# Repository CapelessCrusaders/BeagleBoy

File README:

This project is an entry in the Texas Instruments Intern Design Challenge 2013.
It is a cape for the BeagleBone Black which turns the BBB into a handheld 
gaming console with the addition of an LCD cape stacked on top or a controller
when connected to an HDMI monitor.

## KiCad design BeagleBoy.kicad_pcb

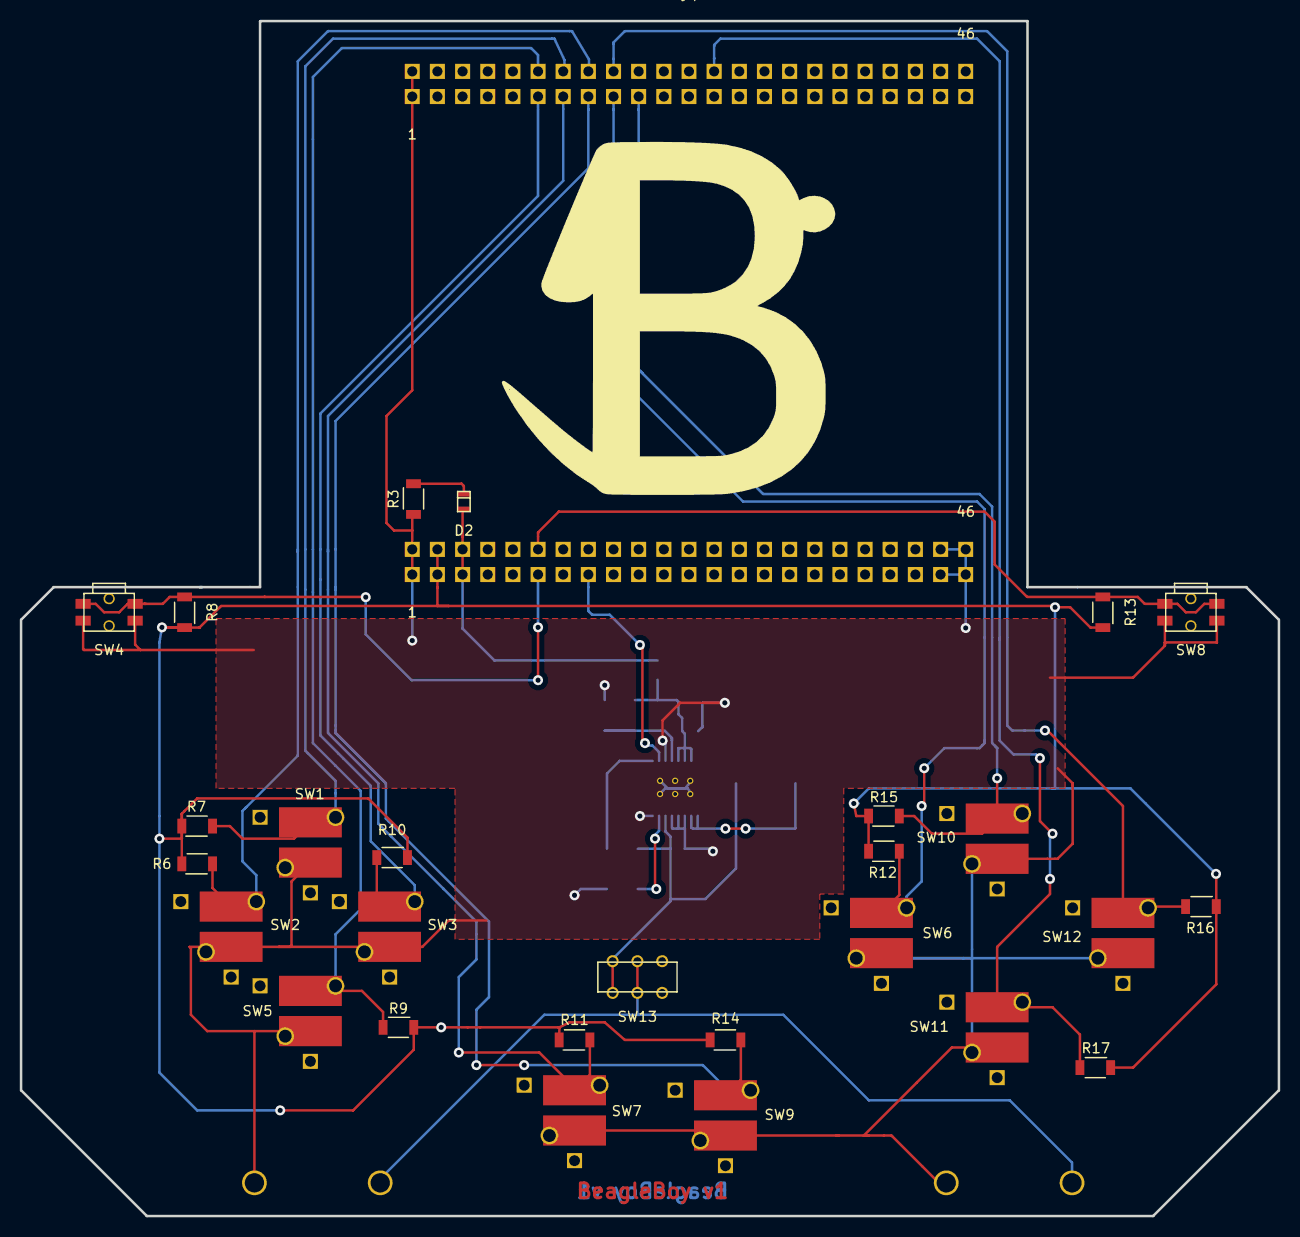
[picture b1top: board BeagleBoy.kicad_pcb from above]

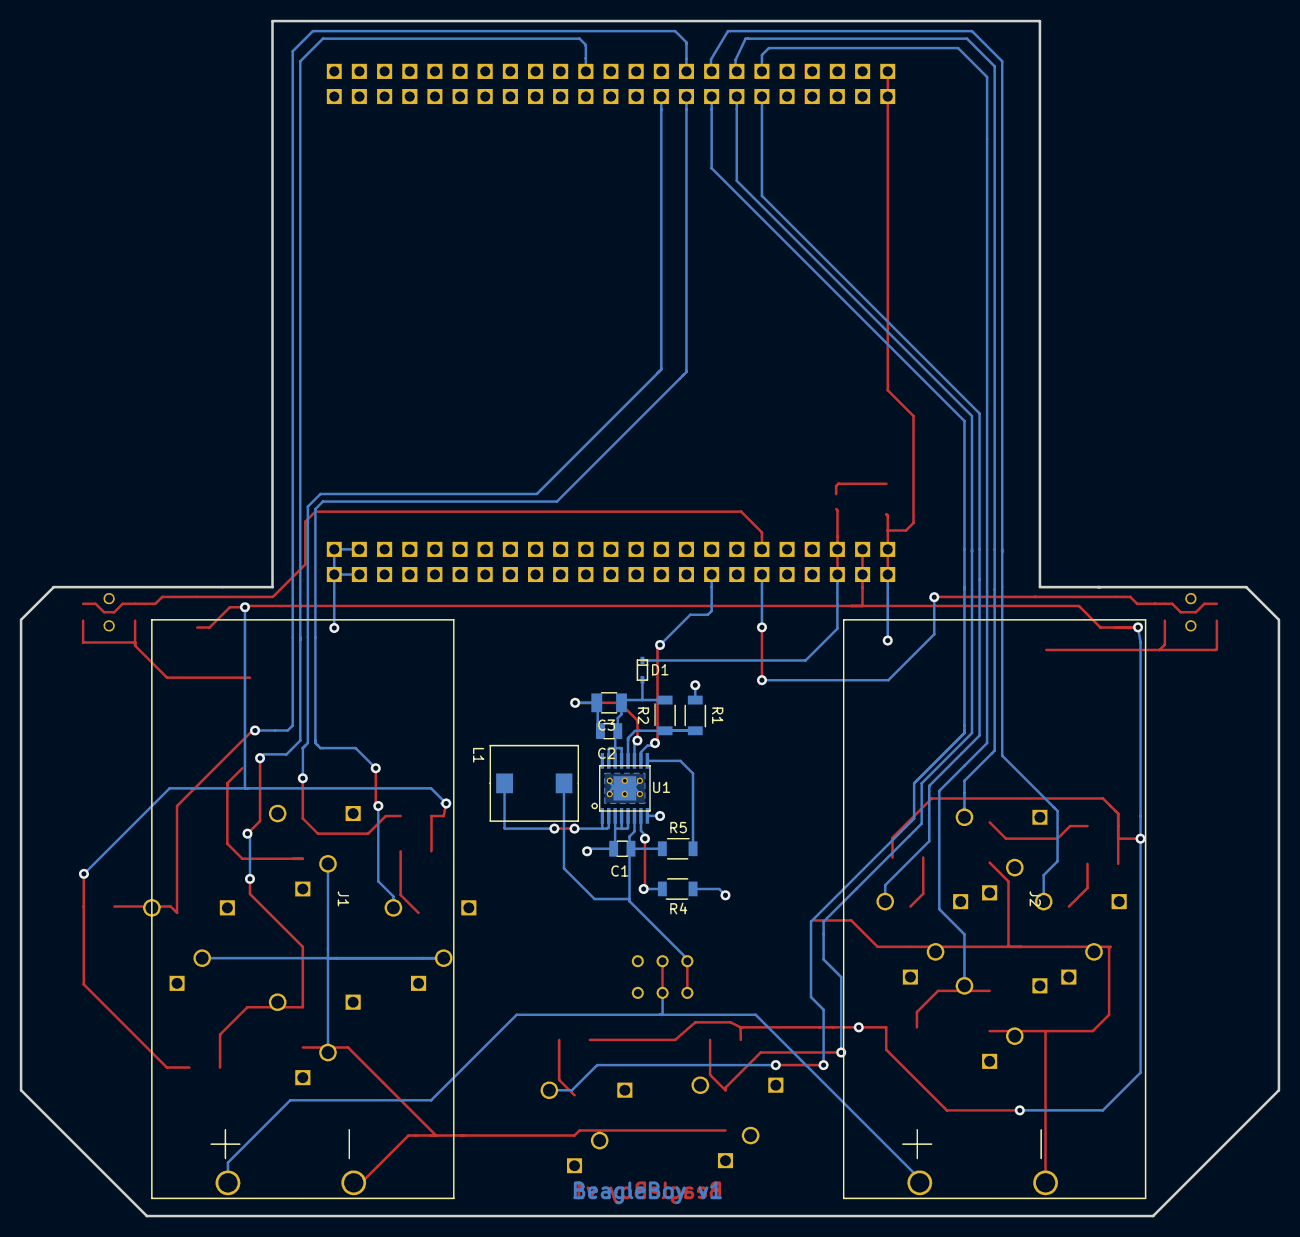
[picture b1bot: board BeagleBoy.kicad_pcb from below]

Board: 2 copper layers, 127.0 x 120.6 mm, 47 parts (12 on the bottom side), 24 nets.

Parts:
C1, C2: 10uF; 0805cap
C3: 47uF; 1206CAP
D1: DIODE_SHOTTKEY; PMEG1020EJ
D2: LED; LTST-C171KGKT
J1, J2: 2AA_BATT; BH2AAPC
J3, J4: 23X2; SSHQ-123-D-**-F-LF
J5, J6, J7, J8, J9, J10: 33MM_PAD; 33mm_pad
L1: 6.8uH; WE-PD
R1: 180K; 1206_resistor
R2: 1.74M; 1206_resistor
R3: 510; 1206_resistor
R4: 0; 1206_resistor
R5, R6, R7, R8, R9, R10, R11, R12, R13, R14, R15, R16, R17: 10K; 1206_resistor
SW1, SW2, SW3, SW5, SW6, SW7, SW9, SW10, SW11, SW12: SPST; SNES_switch
SW4, SW8: SPST_EVQ; EVQ-PUL02K
SW13: SPDT; MHSS1104
U1: TPS61032PWP

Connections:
+3.3V: J3.3, J3.4, R6.2, R7.2, R8.2, R9.2, R10.2, R11.2, R12.2, R13.2, R14.2, R15.2, R16.2, R17.2
+5V: D1.1, D2.1, J3.5, J3.6
+BATT: J1.2, J2.2, SW13.2, SW13.5
/EHRPWM2A: J4.19, R15.1, SW10.1, SW10.3
/EHRPWM2B: J4.13, R11.1, SW7.1, SW7.3
/EN: R5.2, U1.9
/FB: R1.2, R2.1, U1.12
/GPIO0_26: J4.14, R7.1, SW1.1, SW1.3
/GPIO0_27: J4.17, R12.1, SW6.1, SW6.3
/GPIO1_12: J4.12, R9.1, SW5.1, SW5.3
/GPIO1_13: J4.11, R10.1, SW3.1, SW3.3
/GPIO1_14: J4.16, R6.1, SW2.1, SW2.3
/GPIO1_15: J4.15, R14.1, SW9.1, SW9.3
/GPIO1_16: J3.15, U1.10
/GPIO1_28: J3.12, R13.1, SW8.2, SW8.4
/GPIO1_29: J4.26, R17.1, SW11.1, SW11.3
/GPIO2_1: J4.18, R16.1, SW12.1, SW12.3
/LBI: R4.2, U1.7
/SW: L1.2, U1.1, U1.2
/UART4_RXD: J3.11, R8.1, SW4.2, SW4.4
/VBAT: C1.1, L1.1, R5.1, SW13.1, SW13.6, U1.6
/VOUT: C2.1, C3.1, D1.2, R2.2, U1.13, U1.14, U1.15
GND: C1.2, C2.2, C3.2, J1.1, J2.1, J3.1, J3.2, J3.43, J3.44, J3.45, J3.46, J4.1, J4.2, J5.1, J6.1, J7.1, J8.1, J9.1, J10.1, R1.1, R3.1, R4.1, SW1.2, SW1.4, SW2.2, SW2.4, SW3.2, SW3.4, SW4.1, SW4.3, SW5.2, SW5.4, SW6.2, SW6.4, SW7.2, SW7.4, SW8.1, SW8.3, SW9.2, SW9.4, SW10.2, SW10.4, SW11.2, SW11.4, SW12.2, SW12.4, U1.3, U1.4, U1.5, U1.8, U1.11, U1.17
unnamed: D2.2, R3.2

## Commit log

2013-07-17 Initial creation of BeagleBoy project
    GIT attributes and README file created.
2013-07-17 Added ELEC files
    Added BeagleBoy schematic and PCB in original KiCad file and PDF form.
    In the interest of true open sourcery, the part and module libraries are
    also included.
2013-07-23 Added mechanical CAD files
    ABS plastic case designed for Beagle Boy
